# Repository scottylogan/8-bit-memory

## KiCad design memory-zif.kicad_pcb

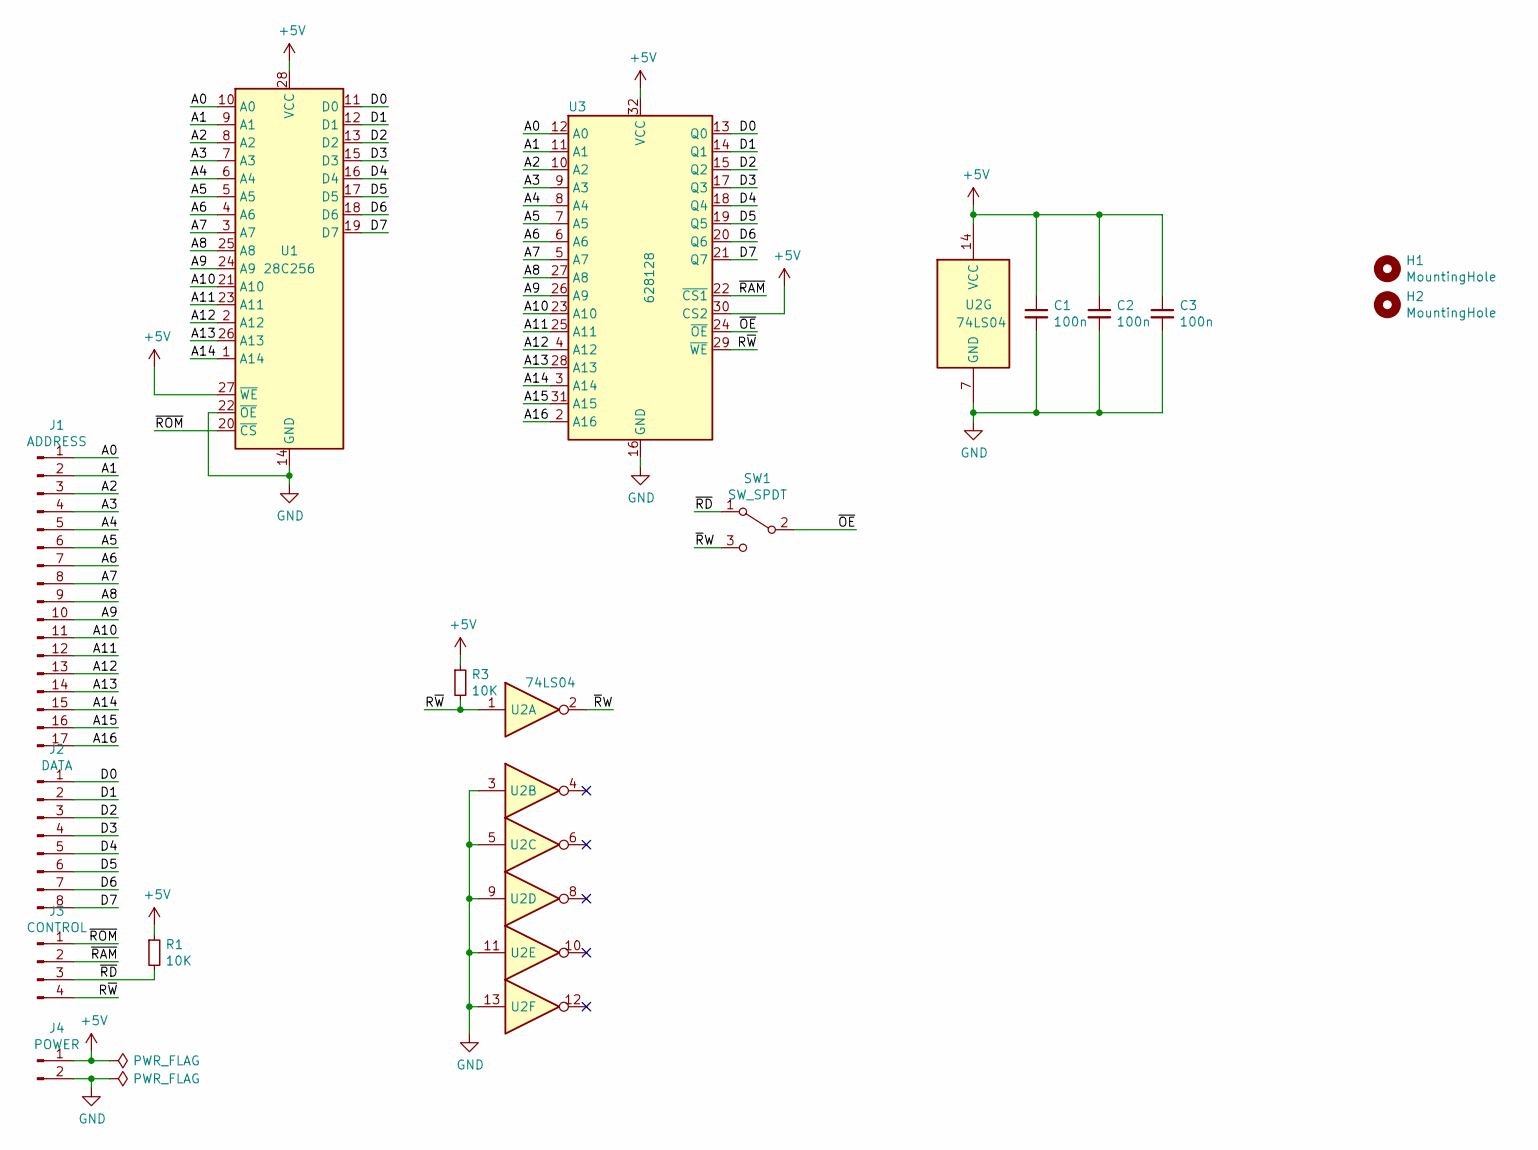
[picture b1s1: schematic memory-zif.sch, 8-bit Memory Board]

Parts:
C1, C2, C3: 100n; C_Disc_D3.0mm_W1.6mm_P2.50mm
H1, H2: MountingHole; MountingHole_3.2mm_M3
J1: ADDRESS; PinHeader_1x17_P2.54mm_Vertical
J2: DATA; PinHeader_1x08_P2.54mm_Vertical
J3: CONTROL; PinHeader_1x04_P2.54mm_Vertical
J4: POWER; PinHeader_1x02_P2.54mm_Vertical
R1, R3: 10K; R_Axial_DIN0204_L3.6mm_D1.6mm_P5.08mm_Horizontal
SW1: SW_SPDT; SWITCH_SPDT_PTH_11.6X4.0MM
U1: 28C256; DIP_Socket-28_W11.9_W12.7_W15.24_W17.78_W18.5_3M_228-1277-0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
U2: 74LS04; DIP-14_W7.62mm_Socket_LongPads
U3: 628128; DIP-32_W15.24mm_Socket_LongPads

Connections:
+5V: C1.1, C2.1, C3.1, J4.1, R1.1, R3.1, U1.27 (~WE), U1.28 (VCC), U2.14 (VCC), U3.30 (CS2), U3.32 (VCC)
/A0: J1.1, U1.10 (A0), U3.12 (A0)
/A1: J1.2, U1.9 (A1), U3.11 (A1)
/A2: J1.3, U1.8 (A2), U3.10 (A2)
/A3: J1.4, U1.7 (A3), U3.9 (A3)
/A4: J1.5, U1.6 (A4), U3.8 (A4)
/A5: J1.6, U1.5 (A5), U3.7 (A5)
/A6: J1.7, U1.4 (A6), U3.6 (A6)
/A7: J1.8, U1.3 (A7), U3.5 (A7)
/A8: J1.9, U1.25 (A8), U3.27 (A8)
/A9: J1.10, U1.24 (A9), U3.26 (A9)
/A10: J1.11, U1.21 (A10), U3.23 (A10)
/A11: J1.12, U1.23 (A11), U3.25 (A11)
/A12: J1.13, U1.2 (A12), U3.4 (A12)
/A13: J1.14, U1.26 (A13), U3.28 (A13)
/A14: J1.15, U1.1 (A14), U3.3 (A14)
/A15: J1.16, U3.31 (A15)
/A16: J1.17, U3.2 (A16)
/D0: J2.1, U1.11 (D0), U3.13 (Q0)
/D1: J2.2, U1.12 (D1), U3.14 (Q1)
/D2: J2.3, U1.13 (D2), U3.15 (Q2)
/D3: J2.4, U1.15 (D3), U3.17 (Q3)
/D4: J2.5, U1.16 (D4), U3.18 (Q4)
/D5: J2.6, U1.17 (D5), U3.19 (Q5)
/D6: J2.7, U1.18 (D6), U3.20 (Q6)
/D7: J2.8, U1.19 (D7), U3.21 (Q7)
/R~W: J3.4, R3.2, U2.1, U3.29 (~WE)
/~OE: SW1.2 (B), U3.24 (~OE)
/~RAM: J3.2, U3.22 (~CS1)
/~RD: J3.3, R1.2, SW1.1 (A)
/~ROM: J3.1, U1.20 (~CS)
/~R~W: SW1.3 (C), U2.2
GND: C1.2, C2.2, C3.2, J4.2, U1.14 (GND), U1.22 (~OE), U2.3, U2.5, U2.7 (GND), U2.9, U2.11, U2.13, U3.16 (GND)

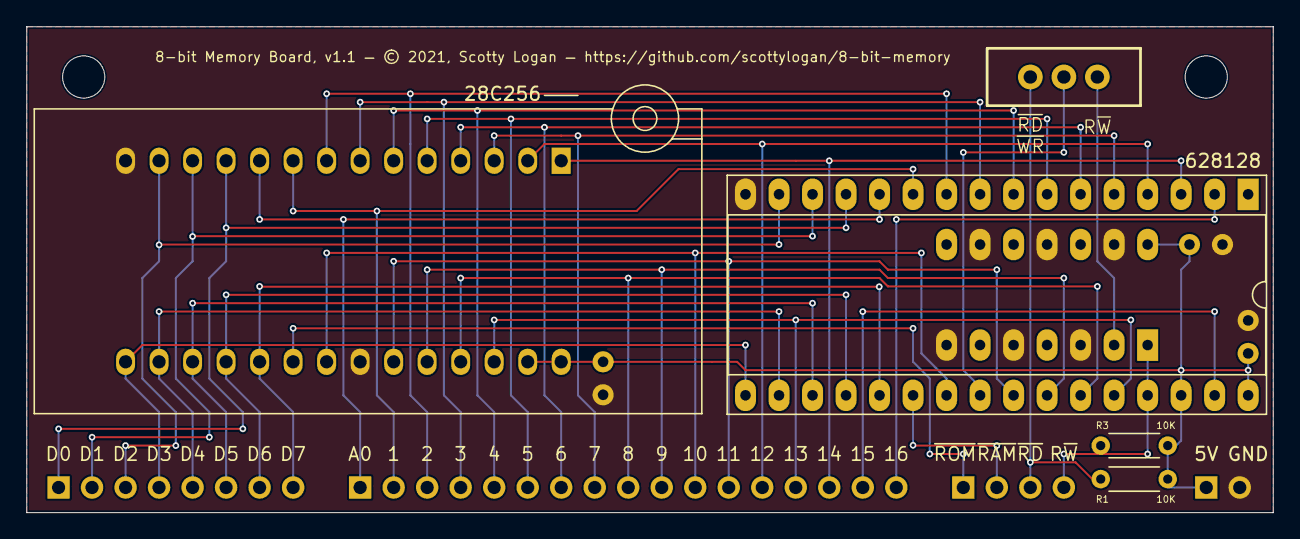
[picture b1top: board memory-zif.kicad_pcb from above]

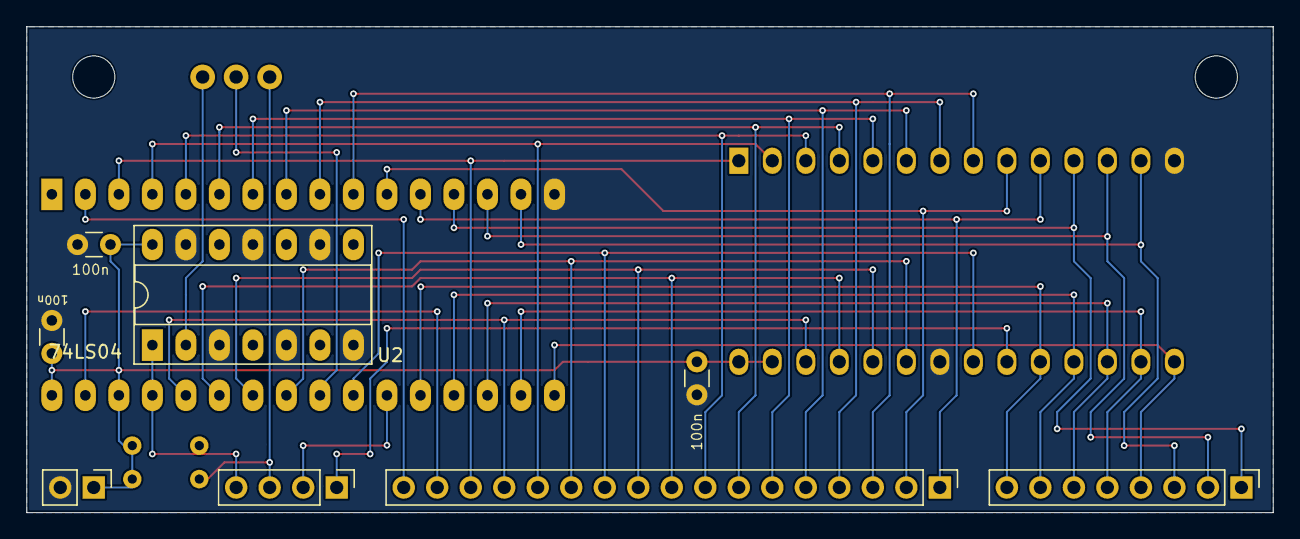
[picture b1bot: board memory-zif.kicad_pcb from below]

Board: 2 copper layers, 94.5 x 36.8 mm, 15 parts (8 on the bottom side), 33 nets.

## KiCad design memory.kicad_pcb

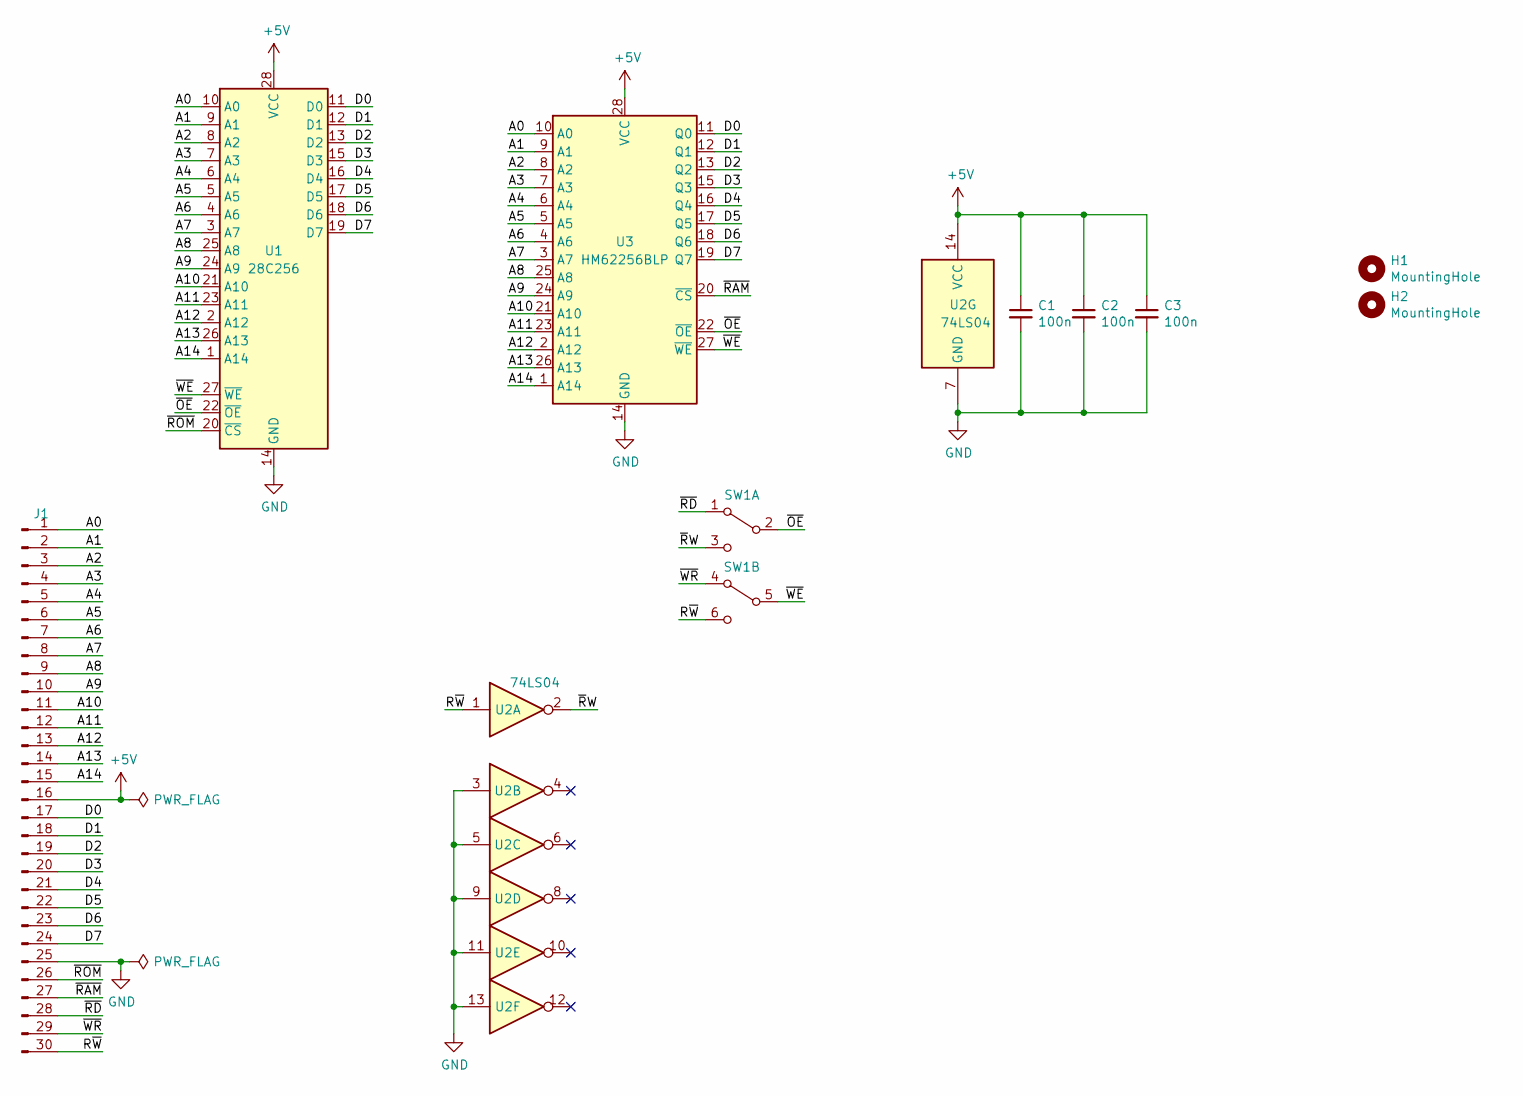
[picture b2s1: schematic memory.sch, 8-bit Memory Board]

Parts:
C1, C2, C3: 100n; C_Disc_D3.0mm_W1.6mm_P2.50mm
H1, H2: MountingHole; MountingHole_3.2mm_M3
J1: Conn_01x30_Male; PinHeader_1x30_P2.54mm_Vertical
SW1: SW_DPDT_x2; SW_E-Switch_EG1271_DPDT
U1: 28C256; DIP-28_W15.24mm_Socket_LongPads
U2: 74LS04; DIP-14_W7.62mm_Socket_LongPads
U3: HM62256BLP; DIP-28_W15.24mm_Socket_LongPads

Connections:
+5V: C1.1, C2.1, C3.1, J1.16, U1.28 (VCC), U2.14 (VCC), U3.28 (VCC)
/A0: J1.1, U1.10 (A0), U3.10 (A0)
/A1: J1.2, U1.9 (A1), U3.9 (A1)
/A2: J1.3, U1.8 (A2), U3.8 (A2)
/A3: J1.4, U1.7 (A3), U3.7 (A3)
/A4: J1.5, U1.6 (A4), U3.6 (A4)
/A5: J1.6, U1.5 (A5), U3.5 (A5)
/A6: J1.7, U1.4 (A6), U3.4 (A6)
/A7: J1.8, U1.3 (A7), U3.3 (A7)
/A8: J1.9, U1.25 (A8), U3.25 (A8)
/A9: J1.10, U1.24 (A9), U3.24 (A9)
/A10: J1.11, U1.21 (A10), U3.21 (A10)
/A11: J1.12, U1.23 (A11), U3.23 (A11)
/A12: J1.13, U1.2 (A12), U3.2 (A12)
/A13: J1.14, U1.26 (A13), U3.26 (A13)
/A14: J1.15, U1.1 (A14), U3.1 (A14)
/D0: J1.17, U1.11 (D0), U3.11 (Q0)
/D1: J1.18, U1.12 (D1), U3.12 (Q1)
/D2: J1.19, U1.13 (D2), U3.13 (Q2)
/D3: J1.20, U1.15 (D3), U3.15 (Q3)
/D4: J1.21, U1.16 (D4), U3.16 (Q4)
/D5: J1.22, U1.17 (D5), U3.17 (Q5)
/D6: J1.23, U1.18 (D6), U3.18 (Q6)
/D7: J1.24, U1.19 (D7), U3.19 (Q7)
/R~W: J1.30, SW1.6 (C), U2.1
/~OE: SW1.2 (B), U1.22 (~OE), U3.22 (~OE)
/~RAM: J1.27, U3.20 (~CS)
/~RD: J1.28, SW1.1 (A)
/~ROM: J1.26, U1.20 (~CS)
/~R~W: SW1.3 (C), U2.2
/~WE: SW1.5 (B), U1.27 (~WE), U3.27 (~WE)
/~WR: J1.29, SW1.4 (A)
GND: C1.2, C2.2, C3.2, J1.25, U1.14 (GND), U2.3, U2.5, U2.7 (GND), U2.9, U2.11, U2.13, U3.14 (GND)

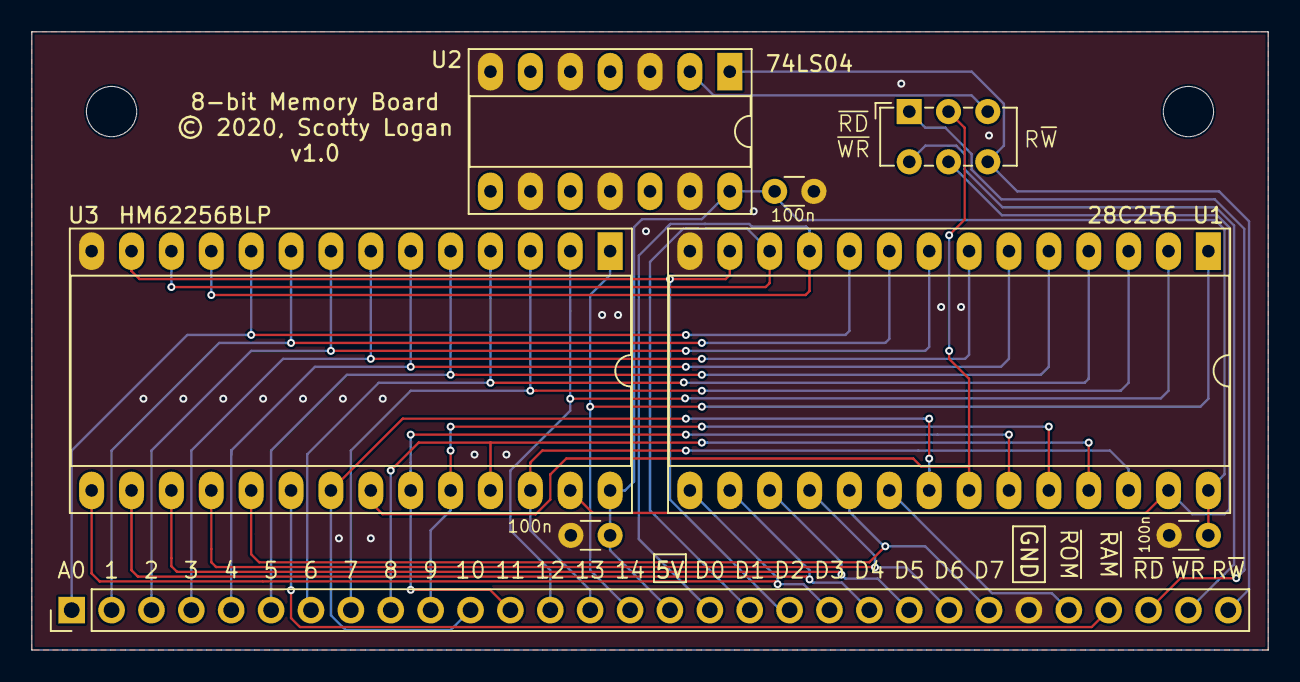
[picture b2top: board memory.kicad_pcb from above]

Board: 2 copper layers, 78.7 x 39.4 mm, 10 parts (0 on the bottom side), 33 nets.

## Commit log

2021-05-05 using 128K RAM rather than 32K RAM
2025-04-16 added LICENSE

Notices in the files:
memory-zif.kicad_pcb:
8-bit Memory Board, v1.1 — © 2021, Scotty Logan — https://github.com/scottylogan/8-bit-memory
memory.kicad_pcb:
© 2020, Scotty Logan
